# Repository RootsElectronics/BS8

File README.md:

# DS8
Coron DS8 Clone.

PCB for (another) Coron DS8 Clone. All ICs and passives are 0603 SMD apart from the CA3080 (DIP Package).
All hardware is PCB mount. 
Fuck off-board wiring. 

Thanks to Bareille, whos through hole clone can be found here:

http://m.bareille.free.fr/ds7clone/ds8.htm

No thanks to Synthrotek.

WARNING
This is currently an unbuilt v0.1

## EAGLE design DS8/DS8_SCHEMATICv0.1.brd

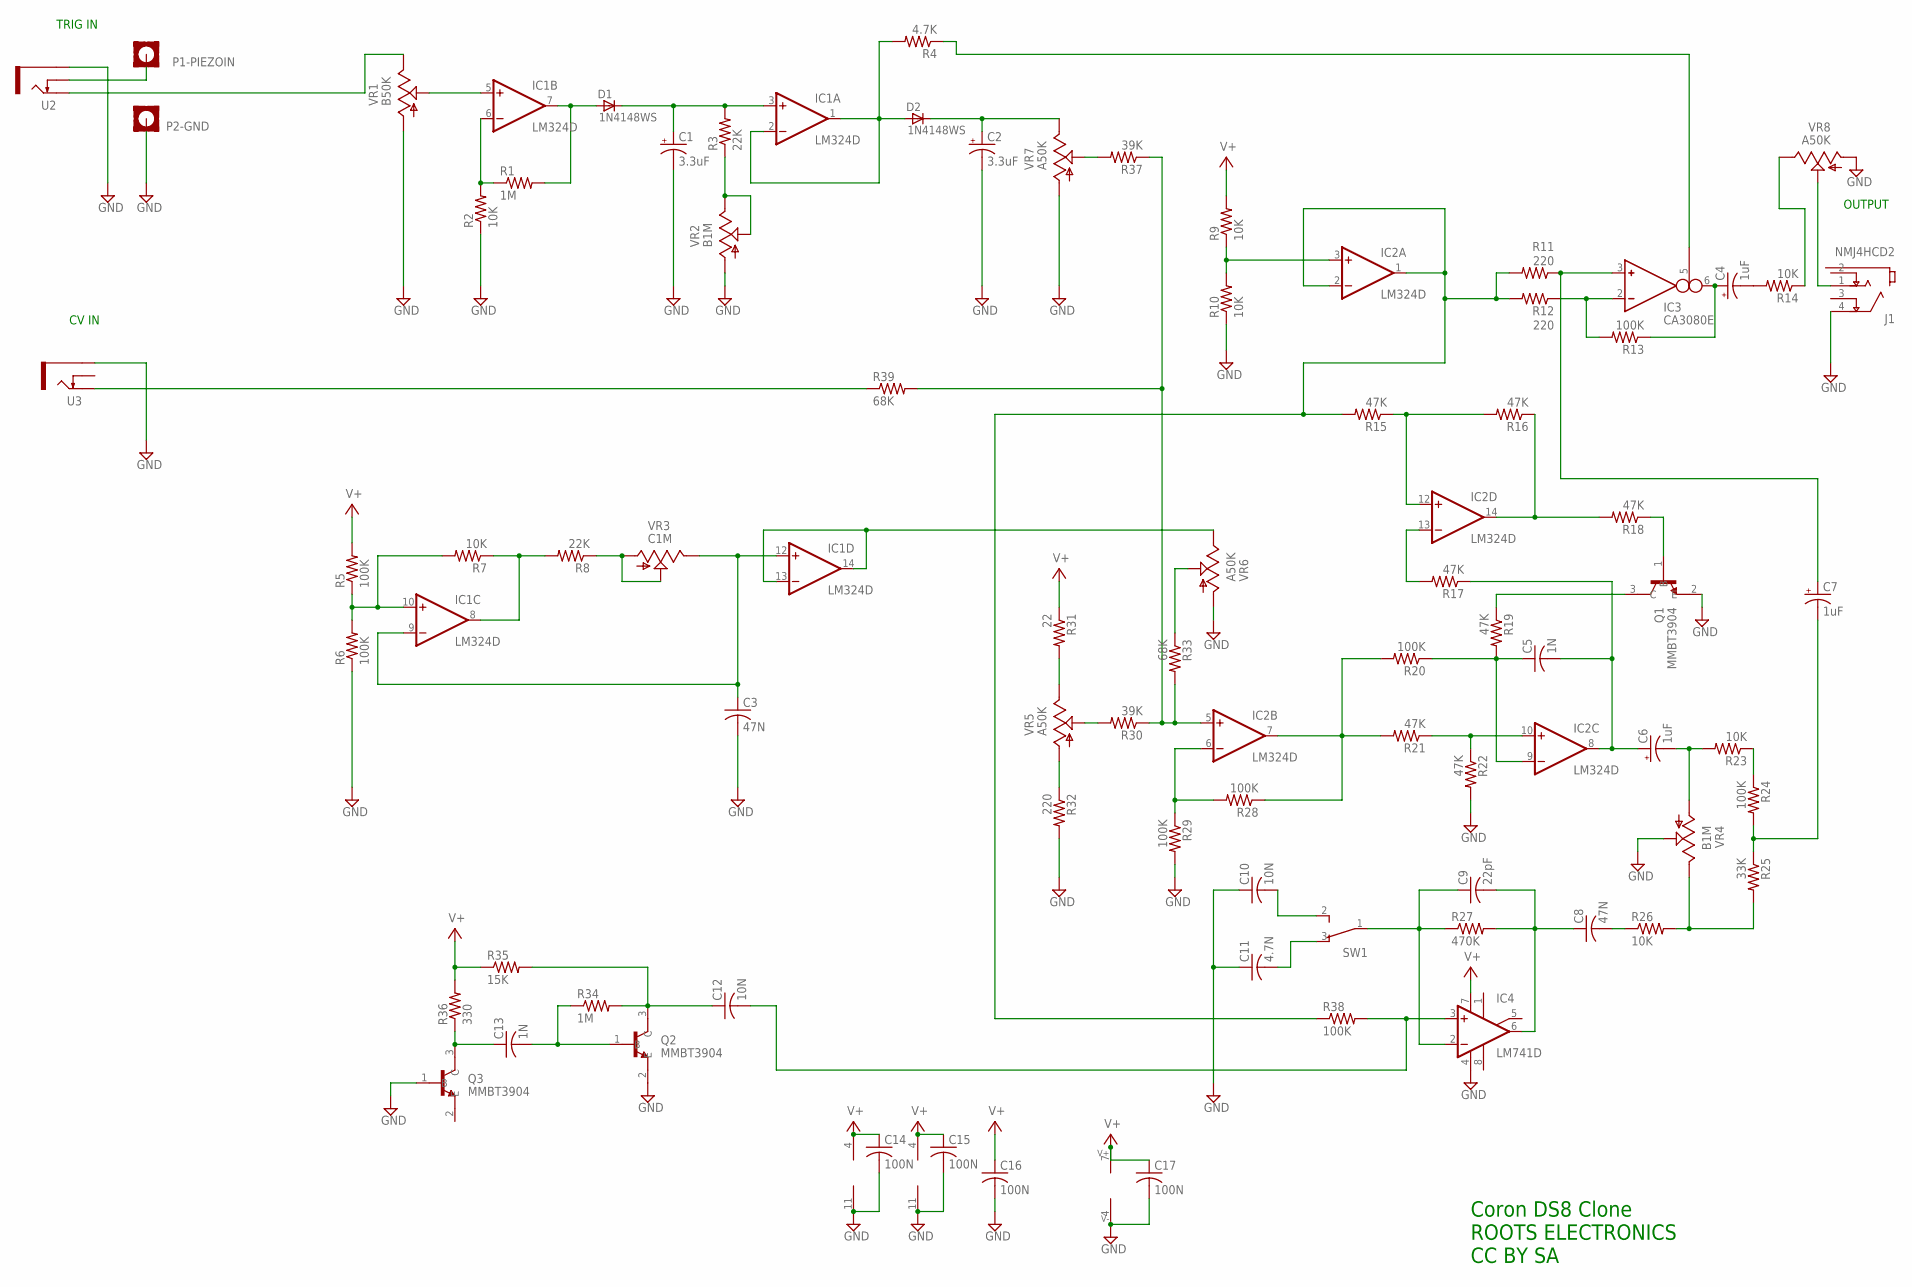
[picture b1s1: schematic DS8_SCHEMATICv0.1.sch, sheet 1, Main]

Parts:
C1, C2: 3.3uF; PANASONIC_C
C3, C8: 47N; C0603
C4, C6, C7: 1uF; PANASONIC_B
C5, C13: 1N; C0603
C9: 22pF; C0603
C10, C12: 10N; C0603
C11: 4.7N; C0603
C14, C15, C16, C17: 100N; C0603
D1, D2: 1N4148WS; SOD323F
IC1, IC2: LM324D; SO14
IC3: CA3080E; DIL08
IC4: LM741D; SO08
J1: NMJ4HCD2; NEUTRIK_NMJ4HCD2
P1-PIEZOIN, P2-GND: MOUNT-PAD-SQUARE2.8; 2,8-PAD-SQUARE
Q1, Q2, Q3: MMBT3904; SOT95P240X120-3N
R1, R34: 1M; R0603
R2, R7, R9, R10, R14, R23, R26: 10K; R0603
R3, R8: 22K; R0603
R4: 4.7K; R0603
R5, R6, R13, R20, R24, R28, R29, R38: 100K; R0603
R11, R12, R32: 220; R0603
R15, R16, R17, R18, R19, R21, R22: 47K; R0603
R25: 33K; R0603
R27: 470K; R0603
R30, R37: 39K; R0603
R31: 22; R0603
R33, R39: 68K; R0603
R35: 15K; R0603
R36: 330; R0603
SW1: 450301014042
U2, U3: THONKICONNNEW; WQP-PJ301M-12_JACK
VR1: B50K; 9MM_SNAP-IN_POT
VR2, VR4: B1M; 9MM_SNAP-IN_POT
VR3: C1M; 9MM_SNAP-IN_POT
VR5, VR6, VR7, VR8: A50K; 9MM_SNAP-IN_POT

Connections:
GND: C1.-, C2.-, C3.2, C10.1, C11.1, C14.2, C15.2, C16.2, C17.2, IC1.11 (V-), IC2.11 (V-), IC3.4 (V-), IC4.4 (V-), J1.4 (S), P2-GND.B2,8, Q1.2 (E), Q2.2 (E), Q3.1 (B), R2.1, R6.1, R10.1, R22.2, R29.2, R32.2, U2.P$3_SLEEVE (SLEEVE), U3.P$3_SLEEVE (SLEEVE), VR1.1 (A), VR2.1 (A), VR4.2 (S), VR6.1 (A), VR7.1 (A), VR8.1 (A); also elsewhere on the board
unnamed: P1-PIEZOIN.B2,8, U2.P$2_SWITCH (SWITCH)
unnamed: U2.P$1_TIP (TIP), VR1.3 (E)
unnamed: IC1.5 (+IN), VR1.2 (S)
unnamed: IC1.6 (-IN), R1.1, R2.2
unnamed: D1.A, IC1.7 (OUT), R1.2
unnamed: C1.+, D1.C, IC1.3 (+IN), R3.2
unnamed: D2.A, IC1.1 (OUT), IC1.2 (-IN), R4.2
unnamed: C2.+, D2.C, VR7.3 (E)
unnamed: R3.1, VR2.2 (S), VR2.3 (E)
unnamed: IC1.10 (+IN), R5.1, R6.2, R7.2
unnamed: IC1.8 (OUT), R7.1, R8.2
unnamed: R8.1, VR3.1 (A), VR3.2 (S)
unnamed: C3.1, IC1.9 (-IN), IC1.12 (+IN), VR3.3 (E)
unnamed: IC1.13 (-IN), IC1.14 (OUT), VR6.3 (E)
unnamed: IC2.3 (+IN), R9.1, R10.2
unnamed: C4.-, R14.2
unnamed: IC2.1 (OUT), IC2.2 (-IN), R11.2, R12.2, R15.2, R38.1
unnamed: IC3.2 (IN_N), R12.1, R13.2
unnamed: C7.+, IC3.3 (IN_P), R11.1
unnamed: C4.+, IC3.6 (OUT), R13.1
unnamed: IC3.5 (I_BIAS), R4.1
unnamed: IC2.12 (+IN), R15.1, R16.2
unnamed: IC2.14 (OUT), R16.1, R18.2
unnamed: IC2.13 (-IN), R17.2
unnamed: Q1.1 (B), R18.1
unnamed: Q1.3 (C), R19.1
unnamed: C5.2, C6.+, IC2.8 (OUT), R17.1
unnamed: C5.1, IC2.9 (-IN), R19.2, R20.1
unnamed: C6.-, R23.2, VR4.1 (A)
unnamed: IC2.10 (+IN), R21.1, R22.1
unnamed: IC2.7 (OUT), R20.2, R21.2, R28.1
unnamed: C7.-, R24.2, R25.1
unnamed: R23.1, R24.1
unnamed: R25.2, R26.2, VR4.3 (E)
unnamed: C8.2, R26.1
unnamed: C8.1, C9.2, IC4.6 (OUT), R27.2
unnamed: C9.1, IC4.2 (-IN), R27.1, SW1.1
unnamed: C10.2, SW1.2
unnamed: C11.2, SW1.3
unnamed: R30.2, VR5.2 (S)
unnamed: IC2.6 (-IN), R28.2, R29.1
unnamed: IC2.5 (+IN), R30.1, R33.2, R37.1, R39.2
unnamed: R32.1, VR5.1 (A)
unnamed: R31.2, VR5.3 (E)
unnamed: R33.1, VR6.2 (S)
unnamed: C12.2, IC4.3 (+IN), R38.2
unnamed: C12.1, Q2.3 (C), R34.2, R35.2
unnamed: C13.2, Q2.1 (B), R34.1
unnamed: C13.1, Q3.3 (C), R36.1
unnamed: R37.2, VR7.2 (S)
unnamed: R14.1, VR8.3 (E)
unnamed: R39.1, U3.P$1_TIP (TIP)
unnamed: J1.1 (T), VR8.2 (S)
V+: C14.1, C15.1, C16.1, C17.1, IC1.4 (V+), IC2.4 (V+), IC3.7 (V+), IC4.7 (V+), R5.2, R9.2, R31.1, R35.1, R36.2; also elsewhere on the board

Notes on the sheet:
CV IN
TRIG IN
OUTPUT
Coron DS8 Clone ROOTS ELECTRONICS CC BY SA

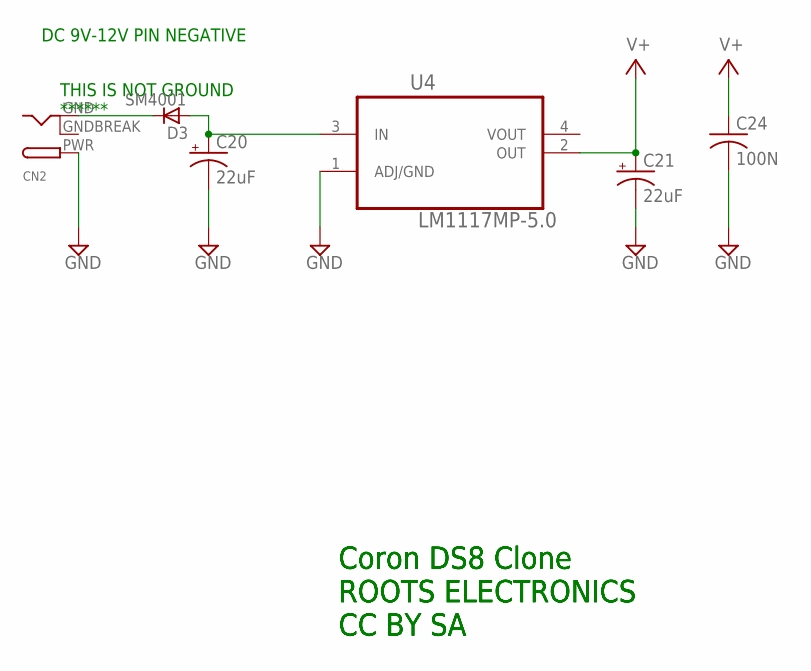
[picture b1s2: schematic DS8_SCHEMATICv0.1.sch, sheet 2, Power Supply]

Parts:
C20, C21: 22uF; PANASONIC_C
C24: 100N; C0603
CN2: DCBARRELPTH; DCJACK_2MM_PTH
D3: SM4001; MELF-MLL41_DO213AB
U4: LM1117MP-5.0; SOT230P696X180-4N

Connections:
GND: C20.-, C21.-, C24.2, CN2.PWR, U4.1 (ADJ/GND); also elsewhere on the board
GNDBREAK: CN2.GNDBREAK
unnamed: CN2.GND, D3.C
unnamed: C20.+, D3.A, U4.3 (IN)
V+: C21.+, C24.1, U4.2 (OUT); also elsewhere on the board

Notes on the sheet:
DC 9V-12V PIN NEGATIVE
THIS IS NOT GROUND ******
Coron DS8 Clone ROOTS ELECTRONICS CC BY SA

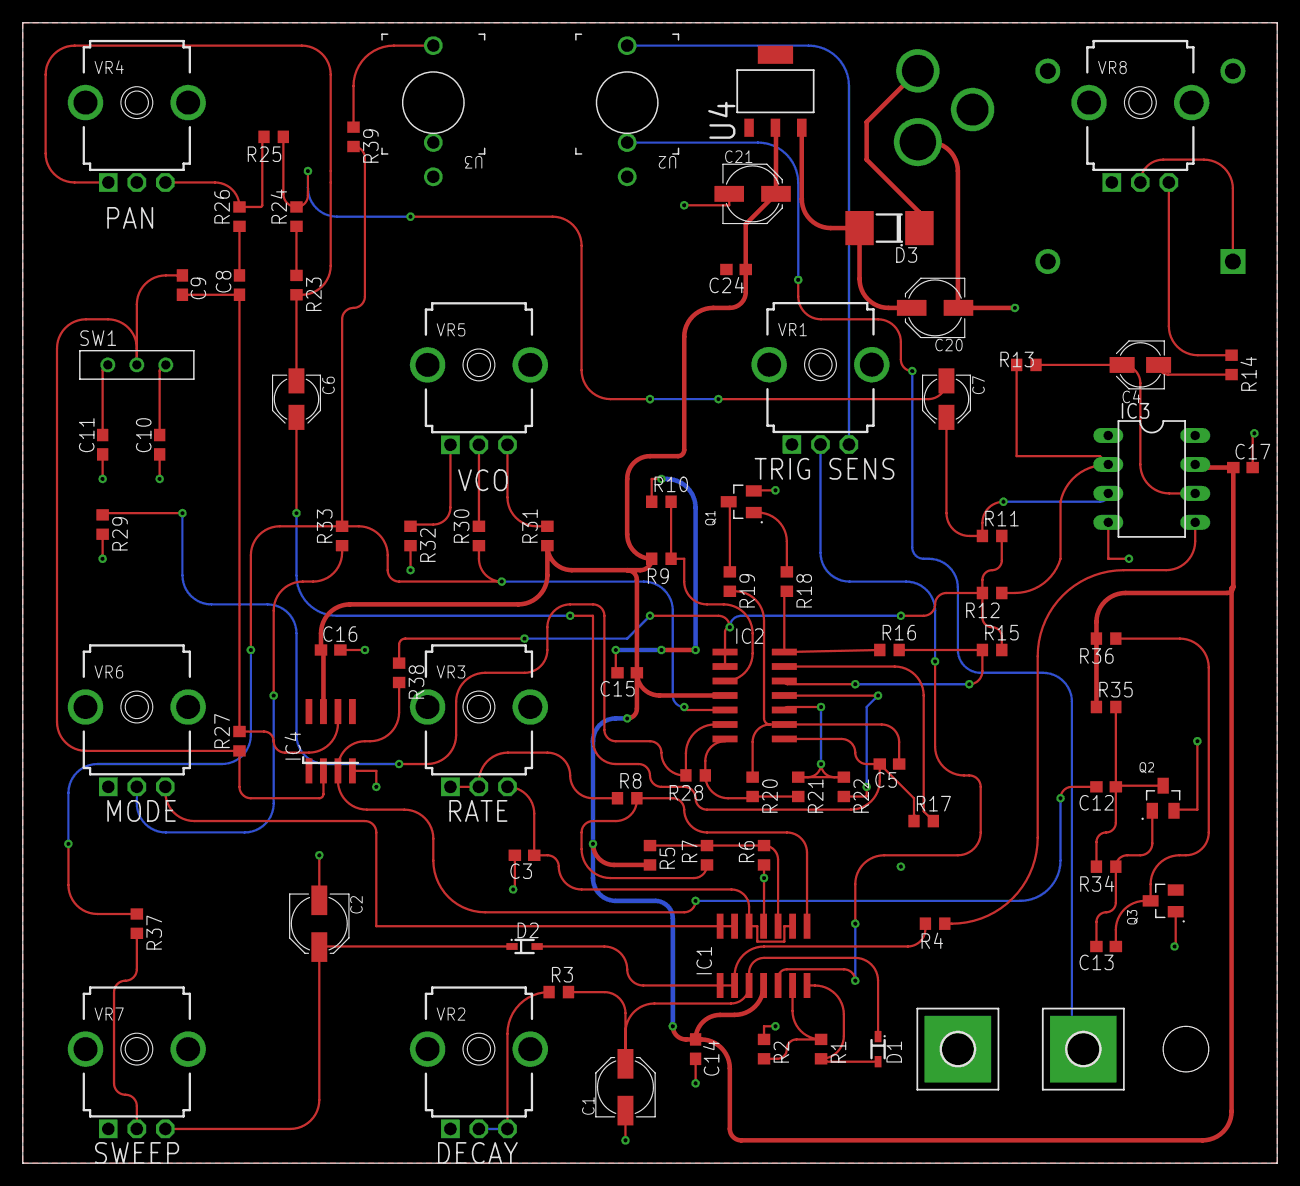
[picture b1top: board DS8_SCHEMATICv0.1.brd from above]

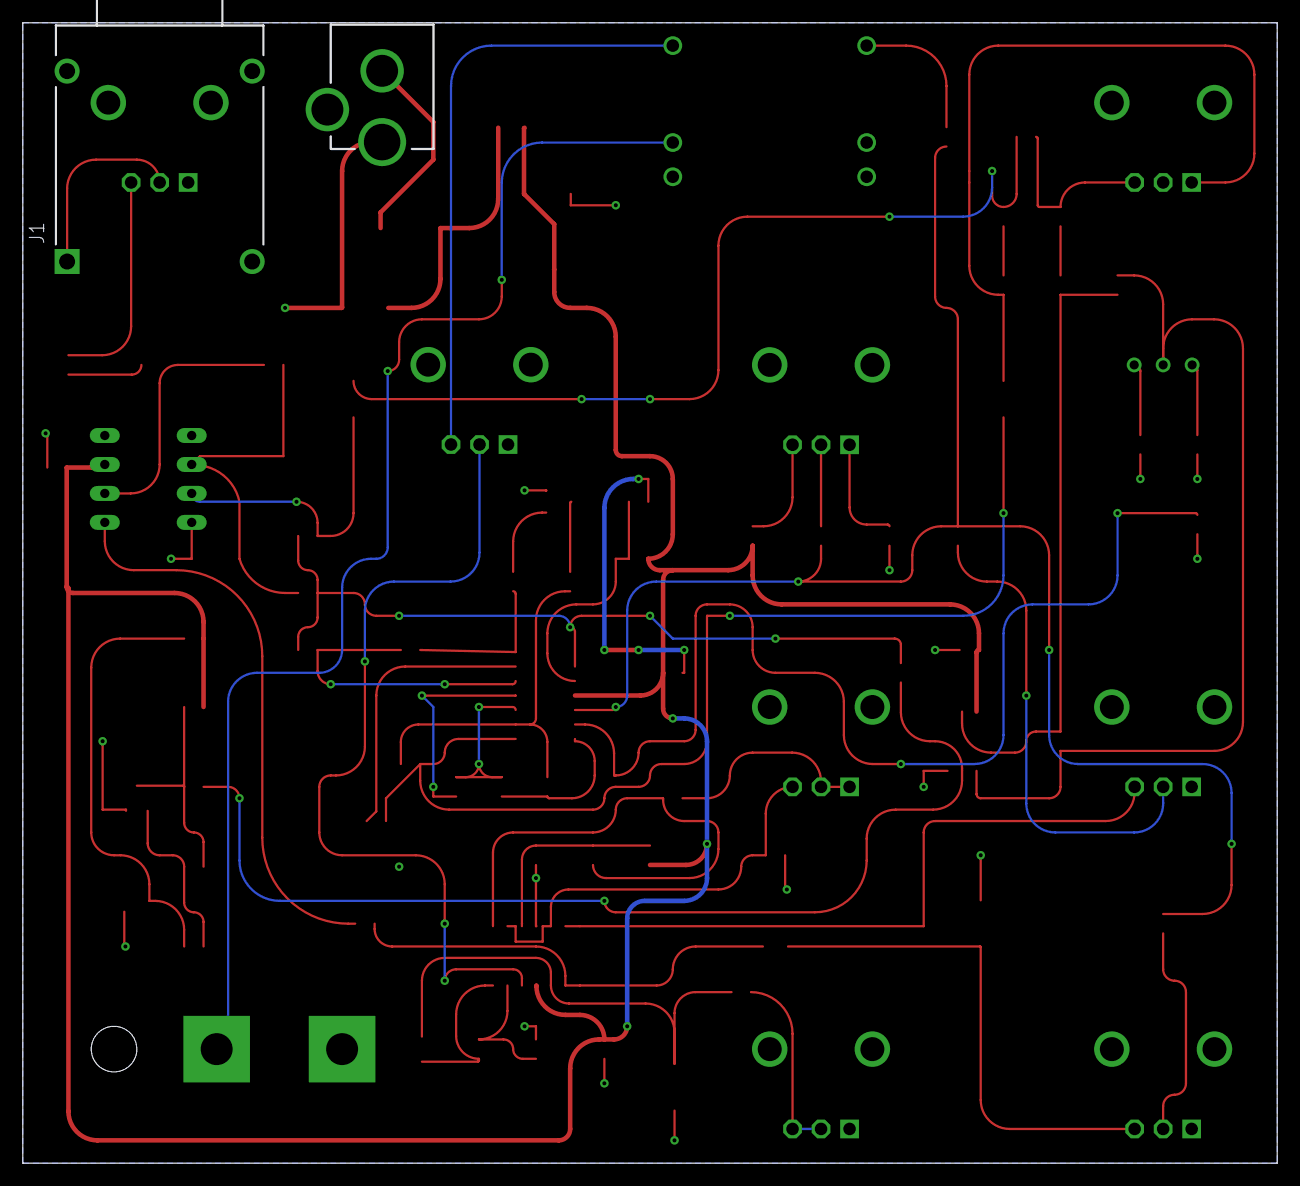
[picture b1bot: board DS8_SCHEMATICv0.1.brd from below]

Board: 2 copper layers, 110.0 x 100.0 mm, 85 parts (2 on the bottom side), 57 nets.

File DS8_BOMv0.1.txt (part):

Partlist exported from C:/Users/jimbo/Documents/EAGLE/projects/DS8/DS8_SCHEMATICv0.1.sch at 27/09/2020 16:44

Qty Value               Device              Package            Parts                                Description                                                                            AVAILABILITY DESCRIPTION                                                                  MF                 MP           PACKAGE                       POPULARITY PRICE PURCHASE-URL                                             
1                       DCBARRELPTH         DCJACK_2MM_PTH     CN2                                  2.0mm DC Barrel Jack                                                                                                                                                                                                                                                                                                     
8   100K                R-US_R0603          R0603              R5, R6, R13, R20, R24, R28, R29, R38 RESISTOR, American symbol                                                                                                                                                                                                                                                                                                
5   100N                C-USC0603           C0603              C14, C15, C16, C17, C24              CAPACITOR, American symbol                                                                                                                                                                                                                                                                                               
7   10K                 R-US_R0603          R0603              R2, R7, R9, R10, R14, R23, R26       RESISTOR, American symbol                                                                                                                                                                                                                                                                                                
2   10N                 C-USC0603           C0603              C10, C12                             CAPACITOR, American symbol                                                                                                                                                                                                                                                                                               
1   15K                 R-US_R0603          R0603              R35                                  RESISTOR, American symbol                                                                                                                                                                                                                                                                                                
2   1M                  R-US_R0603          R0603              R1, R34                              RESISTOR, American symbol                                                                                                                                                                                                                                                                                                
2   1N                  C-USC0603           C0603              C5, C13                              CAPACITOR, American symbol                                                                                                                                                                                                                                                                                               
2   1N4148WS            1N4148WS            SOD323F            D1, D2                               1N4148 General Purpose Rectifie                                                                                                                                                                                                                                                                                          
3   1uF                 CPOL-USB            PANASONIC_B        C4, C6, C7                           POLARIZED CAPACITOR, American symbol                                                                                                                                                                                                                                                                                     
1   22                  R-US_R0603          R0603              R31                                  RESISTOR, American symbol                                                                                                                                                                                                                                                                                                
3   220                 R-US_R0603          R0603              R11, R12, R32                        RESISTOR, American symbol                                                                                                                                                                                                                                                                                                
2   22K                 R-US_R0603          R0603              R3, R8                               RESISTOR, American symbol                                                                                                                                                                                                                                                                                                
1   22pF                C-USC0603           C0603              C9                                   CAPACITOR, American symbol                                                                                                                                                                                                                                                                                               
2   22uF                CPOL-USC            PANASONIC_C        C20, C21                             POLARIZED CAPACITOR, American symbol                                                                                                                                                                                                                                                                                     
2   3.3uF               CPOL-USC            PANASONIC_C        C1, C2                               POLARIZED CAPACITOR, American symbol                                                                                                                                                                                                                                                                                     
1   330                 R-US_R0603          R0603              R36                                  RESISTOR, American symbol                                                                                                                                                                                                                                                                                                
1   33K                 R-US_R0603          R0603              R25                                  RESISTOR, American symbol                                                                                                                                                                                                                                                                                                
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

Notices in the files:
parts and their libraries:
Wurth_Elektronik_Electromechanic_Switchs: Copyright: Würth Elektronik
